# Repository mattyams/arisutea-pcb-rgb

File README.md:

- [X] Edit QMK firmware for v0.4 Arisutea RGB design (07-07-21)
- [X] v0.4 Arisutea RGB PCBs ordered (07-26-21)
- [X] Assemble v0.4 Arisutea RGB PCB once received (11-21-21)
- [X] Assemble Acrylic Case to v0.4 Arisutea RGB design (11-21-21)

## Arisutea RGB Underglow - Arisu Keyboard PCB with More Modifications...now with MORE!

### Disclaimer: Use these files at your own risk!

アリステア PCB designed using KiCad. The layout was originally created by FateNozomi, inspired by Lyn's EM7 and TGR Alice with some modification. The layout was then modified by CorruptedJef and robotictomato to add USB-C, ESD and to shift/add some keys. This inspired me to modify the layout further by adding the ability to swap your switches out whenever you want, make some keys a little more permenant and add some underglow around the edges. If you notice any issue please open an issue and we can discuss!

Since the layout has been modified yet again I decided to give the project a new name, Arisutea, which translates to Alistair. Obviously keeping the theme running here. 

Check out the iBOM [here](https://htmlpreview.github.io/?https://raw.githubusercontent.com/mattyams/arisutea-pcb-rgb/master/hardware/BOM/arisutea-rgb-ibom.html)! This was generated with [InteractiveHtmlBom](https://github.com/openscopeproject/InteractiveHtmlBom)!

Key modifications to the PCB:

- Added in Kailh Hotswap sockets.
- Addition of full backspace position, connected to switch 59 (row 0, column 13).
  - Removed switch 63 and repositioned switch 59 to add full backspace position.
- USB-C ESD rework.
- Added 21 SK6812Mini-E underglow LEDs around the edge.
- Added LED indicators for CAPS and NUM lock as well as layer.
- Updated JSON layout file for this particular keyboard.

Renders generated by [Tracespace](https://github.com/tracespace/tracespace).

v0.4

# QMK Firmware
This can be located in the [firmware](https://github.com/mattyams/arisutea-pcb-rgb/tree/master/firmware) folder. 

# Case Files for Ponoko

Case files are updated to reflect changes to the full backspace on switch 59 and can be found at its repository [arisutea-case](https://github.com/mattyams/arisutea-case).  The most recent case rework works very well with the changes made to the full backspace and addition of the stablizer on the prototypes designed by CorruptedJef and robotictomato. There is now a "boxed" version of the case that is designed to work with some wrist rests that do not have the ortho shape AND case files for version 0.6+ PCBs that include the indicator LEDs.

# FR4 Plates and Case

Additionaly, there are files for FR4 plates to be made and used with this layout. These can be found at its repository [FR4_Plates](https://github.com/mattyams/arisutea-fr4-plates). The plates are designed to fit with the full backspace and non-stepped capslock. That being said, these will not work on the original Fate Designs PCB. No plans to create plates for the LED indicators on the v0.6+ PCBs. NOTE FOR v0.6.3+ PCBs & RGB! FR4 plates still will work but you will have to drill the holes out manually. If you take this route....go forth cautiously adventurer.

## Gerber Files

Download the gerber and BOM files under [releases](https://github.com/mattyams/arisutea-pcb-rgb/releases).

## PCB Assembly

SMT/SMD position files are no longer included for any fab house. There have been too many issues with positions wrong, missing parts, etc.

For the components required, you may refer to the bill of materials included along with the release as reference or load up the design file in KiCad.
All the components can be soldered using a regular soldering iron, though soldering the USB-C receptacle might be the biggest hurdle. Adjustments have been made to the USB footprint to allow for a little more error when handsoldering.  Take care when soldering the LEDs to the board, too much heat can destroy the chip.

## Exceprts from original designer, FateNozomi:

Key differences:

- Removed the extra [B] key on the right half and shifted the [NM,.?] row to the left by 0.25U.
- Shifted the 3 keys to the right and added arrow keys.
- Tweaked the bottom so that the 1.5U keys doesn't protrude out a little.

Shifting the [NM,.?] row to the left by 0.25U required quite some work on the arrangement of keys for the right half.
As a result, this does not give the same typing experience as Lyn's EM7 and TGR Alice.
Lyn's EM7 and TGR Alice uses the home row as the center point to vertically align both halves while I used the number row instead.
Due to the nature of staggered keyboards, aligning using the number row resulted in the home row not being aligned.

Disclaimer: Use these files at your own risk.

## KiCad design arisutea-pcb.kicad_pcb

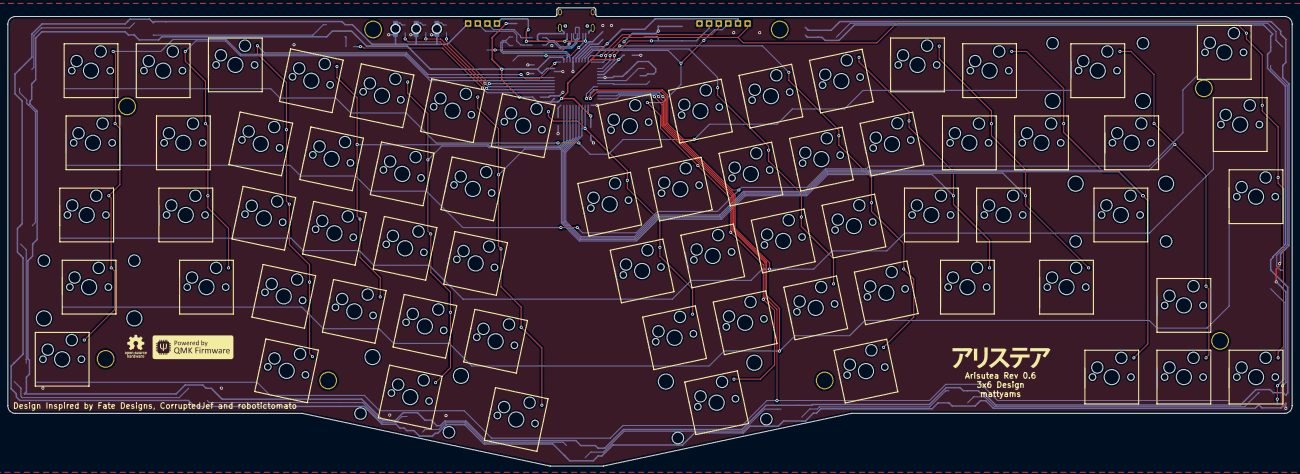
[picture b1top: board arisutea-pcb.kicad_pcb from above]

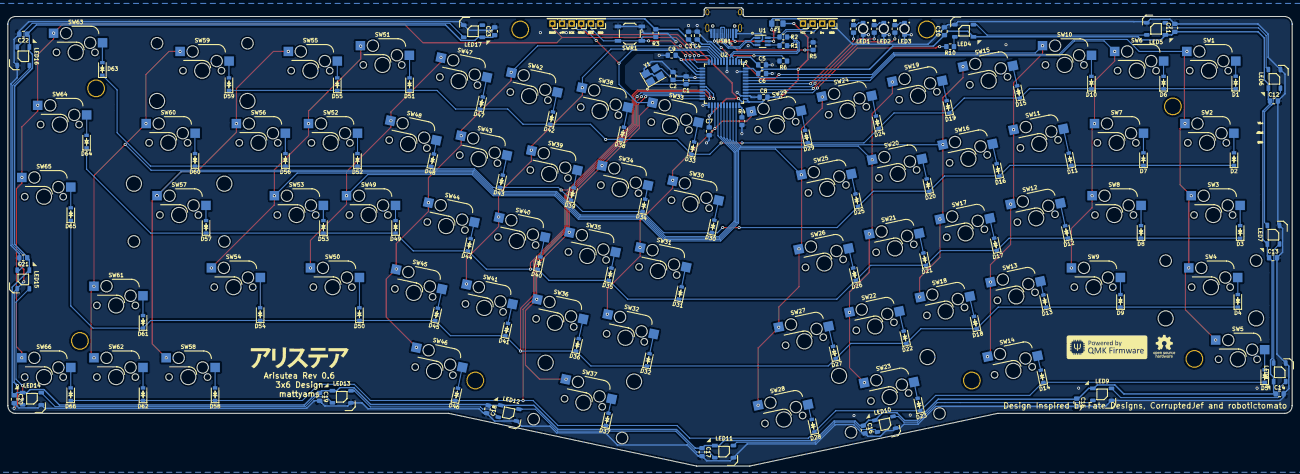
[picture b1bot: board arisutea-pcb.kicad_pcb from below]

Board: 2 copper layers, 339.1 x 121.0 mm, 212 parts (135 on the bottom side), 124 nets.

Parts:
C1, C2: 22pF; C_0805_2012Metric_Pad1.18x1.45mm_HandSolder
C3: 10uF; C_0805_2012Metric_Pad1.18x1.45mm_HandSolder
C4: 1uF (±10%); C_0805_2012Metric_Pad1.18x1.45mm_HandSolder
C5: 1uF; C_0805_2012Metric_Pad1.18x1.45mm_HandSolder
C6, C7, C8, C9, C10, C11, C12, C13, C14, C15, C16, C17, C18, C19, C20, C21, C22, C23: 0.1uF; C_0805_2012Metric_Pad1.18x1.45mm_HandSolder
D1, D2, D3, D4, D5, D6, D7, D8, D9, D10, D11, D12, D13, D14, D15, D16, D17, D18, D19, D20, D21, D22, D23, D24, D25, D26, D27, D28, D29, D30, D31, D32, D33, D34, D35, D36, D37, D38, D39, D40, D41, D42, D43, D44, D45, D46, D47, D48, D49, D50, D51, D52, D53, D54, D55, D56, D57, D58, D59, D60, D61, D62, D63, D64, D65, D66: D; D_SOD-123
F1: 500mA; Fuse_1206_3216Metric_Pad1.42x1.75mm_HandSolder
H1, H2, H3, H4, H5, H6, H7, H8: ThroughHole; Plated_Through_Hole_M2
J2: MISO; PinHeader_1x01_P2.54mm_Vertical
J3: +5V; PinHeader_1x01_P2.54mm_Vertical
J4: SCK; PinHeader_1x01_P2.54mm_Vertical
J5: MOSI; PinHeader_1x01_P2.54mm_Vertical
J6: ~RES~; PinHeader_1x01_P2.54mm_Vertical
J7, J15: GND; PinHeader_1x01_P2.54mm_Vertical
J12: VCC; PinHeader_1x01_P2.54mm_Vertical
J13: D+; PinHeader_1x01_P2.54mm_Vertical
J14: D-; PinHeader_1x01_P2.54mm_Vertical
LED1: NUM_LOCK; LED_IN-S124ARUW
LED2: CAPS_LOCK; LED_IN-S124ARUW
LED3: FN_LED; LED_IN-S124ARUW
LED4, LED5, LED6, LED7, LED8, LED9, LED10, LED11, LED12, LED13, LED14, LED15, LED16, LED17: WS2812B; LED_WS2812B
LOGO1, LOGO2: arisutea_logo
LOGO3, LOGO4: arisutea_logo; OSHW-Logo_5.7x6mm_SilkScreen
LOGO5: arisutea_logo; QMK_Logo_Dark
LOGO6: QMK_LOGO; QMK_Logo_Dark
R1, R2: 22; R_0805_2012Metric_Pad1.20x1.40mm_HandSolder
R3, R4: 10K; R_0805_2012Metric_Pad1.20x1.40mm_HandSolder
R5, R6: 5k1; R_0805_2012Metric_Pad1.20x1.40mm_HandSolder
R7, R8, R9: 470; R_0805_2012Metric_Pad1.20x1.40mm_HandSolder
R10: 720; R_0805_2012Metric_Pad1.20x1.40mm_HandSolder
SW1, SW6, SW7, SW8, SW9, SW10, SW11, SW12, SW13, SW14, SW15, SW16, SW17, SW18, SW19, SW20, SW21, SW22, SW24, SW25, SW26, SW27, SW28, SW29, SW30, SW31, SW32, SW33, SW34, SW35, SW36, SW38, SW39, SW40, SW41, SW42, SW43, SW44, SW45, SW46, SW47, SW48, SW49, SW50, SW51, SW52, SW53, SW55, SW56, SW58, SW61, SW62, SW63, SW64, SW65, SW66: SW_Push; SW_Hotswap_Kailh_1.00u
SW2, SW5, SW60: SW_Push; SW_Hotswap_Kailh_1.50u
SW3, SW54: SW_Push; SW_Hotswap_Kailh_1.75u
SW4: SW_Push; SW_Hotswap_Kailh_2.25u
SW23: SW_Push; SW_Hotswap_Kailh_2.00u_RevStab
SW37: SW_Push; SW_Hotswap_Kailh_2.75u_RevStab
SW57: SW_Push; SW_Hotswap_Kailh_2.25u_RevStab
SW59: SW_Push; SW_Hotswap_Kailh_2.00u
SWR1: SW_Push; SW_SPST_TL3342
U1: USBLC6-2SC6; SOT-23-6_Handsoldering
U2: ATmega32U4-AU; TQFP-44_10x10mm_P0.8mm
USB1: USB_C_HRO_TYPE-C-31-M-12-USB_Type-C; USB_C_Receptacle_HRO_TYPE-C-31-M-12-HandSoldering
Y1: Crystal_GND24; Crystal_SMD_TXC_7M-4Pin_3.2x2.5mm_HandSoldering

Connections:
+5V: C3.1, C5.1, C6.1, C7.1, C8.1, C9.1, C10.1, C11.1, C12.1, C13.1, C14.1, C15.1, C16.1, C17.1, C18.1, C19.1, C20.1, C21.1, C22.1, C23.1, F1.1, J3.1, LED4.1, LED5.1, LED6.1, LED7.1, LED8.1, LED9.1, LED10.1, LED11.1, LED12.1, LED13.1, LED14.1, LED15.1, LED16.1, LED17.1, R3.1, U2.2, U2.7, U2.14, U2.24, U2.34, U2.44
/MISO: J2.1, SW63.2, SW64.2, SW65.2, SW66.2, U2.11
/MOSI: J5.1, U2.10
/SCK: J4.1, SW33.2, SW34.2, SW35.2, SW36.2, SW37.2, U2.9
/col0: SW1.2, SW2.2, SW3.2, SW4.2, SW5.2, U2.41
/col1: SW6.2, SW7.2, SW8.2, SW9.2, U2.40
/col2: SW10.2, SW11.2, SW12.2, SW13.2, SW14.2, U2.1
/col3: SW15.2, SW16.2, SW17.2, SW18.2, U2.32
/col4: SW19.2, SW20.2, SW21.2, SW22.2, SW23.2, U2.31
/col5: SW24.2, SW25.2, SW26.2, SW27.2, SW28.2, U2.30
/col6: SW29.2, SW30.2, SW31.2, SW32.2, U2.25
/col8: SW38.2, SW39.2, SW40.2, SW41.2, U2.8
/col9: SW42.2, SW43.2, SW44.2, SW45.2, SW46.2, U2.12
/col10: SW47.2, SW48.2, SW49.2, SW50.2, U2.29
/col11: SW51.2, SW52.2, SW53.2, SW54.2, U2.28
/col12: SW55.2, SW56.2, SW57.2, SW58.2, U2.27
/col13: SW59.2, SW60.2, SW61.2, SW62.2, U2.26
/row0: D1.1, D6.1, D10.1, D15.1, D19.1, D24.1, D29.1, D33.1, D38.1, D42.1, D47.1, D51.1, D55.1, D59.1, U2.18
/row1: D2.1, D7.1, D11.1, D16.1, D20.1, D25.1, D30.1, D34.1, D39.1, D43.1, D48.1, D52.1, D56.1, D60.1, D63.1, U2.19
/row2: D3.1, D8.1, D12.1, D17.1, D21.1, D26.1, D31.1, D35.1, D40.1, D44.1, D49.1, D53.1, D57.1, D64.1, U2.20
/row3: D4.1, D9.1, D13.1, D18.1, D22.1, D27.1, D32.1, D36.1, D41.1, D45.1, D50.1, D54.1, D61.1, D65.1, U2.21
/row4: D5.1, D14.1, D23.1, D28.1, D37.1, D46.1, D58.1, D62.1, D66.1, U2.22
/~RES~: J6.1, R3.2, SWR1.2, U2.13
CAPS_L: R8.2, U2.38
D+: R1.1, U2.4
D-: R2.1, U2.3
FN_L: R7.2, U2.39
GND: C1.1, C2.2, C3.2, C4.2, C5.2, C6.2, C7.2, C8.2, C9.2, C10.2, C11.2, C12.2, C13.2, C14.2, C15.2, C16.2, C17.2, C18.2, C19.2, C20.2, C21.2, C22.2, C23.2, J7.1, J15.1, LED1.C, LED2.C, LED3.C, LED4.3, LED5.3, LED6.3, LED7.3, LED8.3, LED9.3, LED10.3, LED11.3, LED12.3, LED13.3, LED14.3, LED15.3, LED16.3, LED17.3, R4.2, R5.2, R6.2, SWR1.1, U1.2, U2.5, U2.15, U2.23, U2.35, U2.43, USB1.A1, USB1.A12, USB1.S1, Y1.2, Y1.4
NUM_L: R9.2, U2.37
unnamed: C4.1, U2.6
unnamed: D1.2, SW1.1
unnamed: D2.2, SW2.1
unnamed: D3.2, SW3.1
unnamed: D4.2, SW4.1
unnamed: D5.2, SW5.1
unnamed: D6.2, SW6.1
unnamed: D7.2, SW7.1
unnamed: D8.2, SW8.1
unnamed: D9.2, SW9.1
unnamed: D10.2, SW10.1
unnamed: D11.2, SW11.1
unnamed: D12.2, SW12.1
unnamed: D13.2, SW13.1
unnamed: D14.2, SW14.1
unnamed: D15.2, SW15.1
unnamed: D16.2, SW16.1
unnamed: D17.2, SW17.1
unnamed: D18.2, SW18.1
unnamed: D19.2, SW19.1
unnamed: D20.2, SW20.1
unnamed: D21.2, SW21.1
unnamed: D22.2, SW22.1
unnamed: D23.2, SW23.1
unnamed: D24.2, SW24.1
unnamed: D25.2, SW25.1
unnamed: D26.2, SW26.1
unnamed: D27.2, SW27.1
unnamed: D28.2, SW28.1
unnamed: D29.2, SW29.1
unnamed: D30.2, SW30.1
unnamed: D31.2, SW31.1
unnamed: D32.2, SW32.1
unnamed: D33.2, SW33.1
unnamed: D34.2, SW34.1
unnamed: D35.2, SW35.1
unnamed: D36.2, SW36.1
unnamed: D37.2, SW37.1
unnamed: D38.2, SW38.1
unnamed: D39.2, SW39.1
unnamed: D40.2, SW40.1
unnamed: D41.2, SW41.1
unnamed: D42.2, SW42.1
unnamed: D43.2, SW43.1
unnamed: D44.2, SW44.1
unnamed: D45.2, SW45.1
unnamed: D46.2, SW46.1
unnamed: D47.2, SW47.1
unnamed: D48.2, SW48.1
unnamed: D49.2, SW49.1
unnamed: D50.2, SW50.1
unnamed: D51.2, SW51.1
unnamed: D52.2, SW52.1
unnamed: D53.2, SW53.1
unnamed: D54.2, SW54.1
unnamed: D55.2, SW55.1
unnamed: D56.2, SW56.1
unnamed: D57.2, SW57.1
unnamed: D58.2, SW58.1
unnamed: D59.2, SW59.1
unnamed: D60.2, SW60.1
unnamed: D61.2, SW61.1
unnamed: D62.2, SW62.1
unnamed: D63.2, SW63.1
unnamed: D64.2, SW64.1
unnamed: D65.2, SW65.1
unnamed: D66.2, SW66.1
unnamed: J13.1, R1.2, U1.4
unnamed: J14.1, R2.2, U1.6
unnamed: LED1.A, R7.1
unnamed: LED2.A, R8.1
unnamed: LED3.A, R9.1
unnamed: LED4.2, LED5.4
unnamed: LED4.4, R10.1
unnamed: LED5.2, LED6.4
unnamed: LED6.2, LED7.4
unnamed: LED7.2, LED8.4
unnamed: LED8.2, LED9.4
unnamed: LED10.2, LED11.4
unnamed: LED9.2, LED10.4
unnamed: LED11.2, LED12.4
unnamed: LED12.2, LED13.4
unnamed: LED13.2, LED14.4
unnamed: LED14.2, LED15.4
unnamed: LED15.2, LED16.4
unnamed: LED16.2, LED17.4
unnamed: R4.1, U2.33
unnamed: R5.1, USB1.A5
unnamed: R6.1, USB1.B5
unnamed: U1.1, USB1.A7, USB1.B7
unnamed: U1.3, USB1.A6, USB1.B6
RGB: R10.2, U2.36
VCC: F1.2, J12.1, U1.5, USB1.A4, USB1.A9
XTAL1: C1.2, U2.17, Y1.1
XTAL2: C2.1, U2.16, Y1.3

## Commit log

2021-03-04 USB-C, hotswaps, ESD update, plates, so much
    Added USB-C, updated case files, ESD rework, FR4 plates made, name change, hotswap sockets, route rework
2021-03-04 Update LICENSE
2021-03-04 Delete diode_position.txt
    not needed
2021-03-07 routing rework, mounting holes changed, add power LED, crystal adjustment
    Moved some routes around...again. Changed the mounting holes to through holes for plate mounting. Added a power LED, because why not? Adjusted the crystal placement.
2021-03-07 adjusted mask, added gerbers
2021-03-07 fixed silly routing mistake
2021-03-07 house keeping, fixed another silly routing mistake, regen gerbs and BOM
2021-03-07 add some keeb images
2021-03-07 update name
2021-03-07 add kicad images for plates
2021-03-07 update case files for matte option, update readmes
2021-03-08 footprint and trace cleanup
    Changed some footprints to show clearer positioning of U1, U2 and Y1 as well as all the key switch diodes on the silkscreen.
    Correct footprint and name for LED.
    Moved a couple of traces around slightly for aesthetics.
    Removed some trace tails that were just hanging out.
2021-03-10 correct json for layout
2021-03-10 update readme to add FR4 plate pics
2021-03-12 fix some routing boo boos and added boxed case design
2021-03-12 updated gerbies
2021-03-14 FR4 plate assembly and case update
2021-03-16 update photos
2021-03-21 versioning to 0.4
    remove LED...../sigh
2021-03-21 align version numbers
2021-03-21 update switch positions to be more uniform
2021-03-22 BOM and position files update
2021-03-23 library, silkscreen and gerber update
    I moved all the footprints into a single library so that if folks don't have the particular lib they won't have to go and search for it or try to replace. Silkscreen was updated again to show clearer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
2021-03-24 footprint and 3d model updates
2021-03-25 0.5 update
    Fixes some routing that really did not need to be fixed but my OCD was screaming at me. Fixes an issue with the USB port only being shown as a through hole component and not an SMD. Reup gerbies, BOM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
2021-03-27 added LED strip and indicator support, new cases for indicators
2021-03-29 add firmware files
2021-03-30 WS2812 PADS ADDED
2021-05-24 Rev 0.2
    Changed LEDs to SK6812Mini-E and rerouted.
2021-05-25 add iBOM
2021-06-19 Rev 0.3
    Might send this one out to get made. Not sure yet.
    - Added 2 more LEDs to the edge and positioned them to be a little more evenly spread out.
    - Rerouted all LED traces for better aesthetics and functionality.
    - Increased power trace size. This might not be needed but it can't hurt to add with the addition of the LEDs.
    - Removed programming headers. This was a personal decision as I never used them or found a need for them. It helped free up some space to route LEDs.
    - Updated library, images, gerbies and BOM.
2021-07-09 smol update
2021-07-23 added MOAR LEDZZZZZZZZZ
    5 more to be exact.
2021-07-25 added different logo, redid gerbies
2021-08-11 Rev 0.4
    Added more LEDs, moved some traces around, updated iBOM, added new renders...and things
2021-08-11 Removed arisutea-case and FR4_plates to replace with submodule
2021-08-11 Replaced case and fr4-plates directory with submodules
2021-08-11 remove plate gerbers
    These can be found in the plates subfolder gerber folder now.
2021-08-11 Update arisutea-fr4-plates
2021-12-19 Update README.md
    Update for v0.4 build.
    Removed a lot of "I" wording.
2021-12-20 Kicad version bump
2021-12-20 Added LGUI key
    Community request to add a LGUI key to the board.
    Added new key.
    Rerouted.
    Moved logos.
2021-12-20 add pretty logo
2022-01-18 updated gerbers and bom
2022-01-19 updated gerbers to correct fab house caps, update submodules
2022-01-19 actually updated submodules this time
